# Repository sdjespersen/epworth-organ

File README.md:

# Epworth Organ

Encoders (`primary-encoder` being the primary), decoders (`primary-decoder` being the primary), etc. for the Epworth
organ, targeting the [Raspberry Pi Pico 2](https://datasheets.raspberrypi.com/pico/pico-2-datasheet.pdf), written in
Rust.

## Setup

The best dev setup for this involves using a
[Pico debug probe](https://www.raspberrypi.com/documentation/microcontrollers/debug-probe.html)
and [probe-rs](https://probe.rs). This allows you to get a SWD debugger and UART output, as well as flashing the program
to the chip without holding BOOTSEL while plugging in the USB. (Trust me, it gets old!)

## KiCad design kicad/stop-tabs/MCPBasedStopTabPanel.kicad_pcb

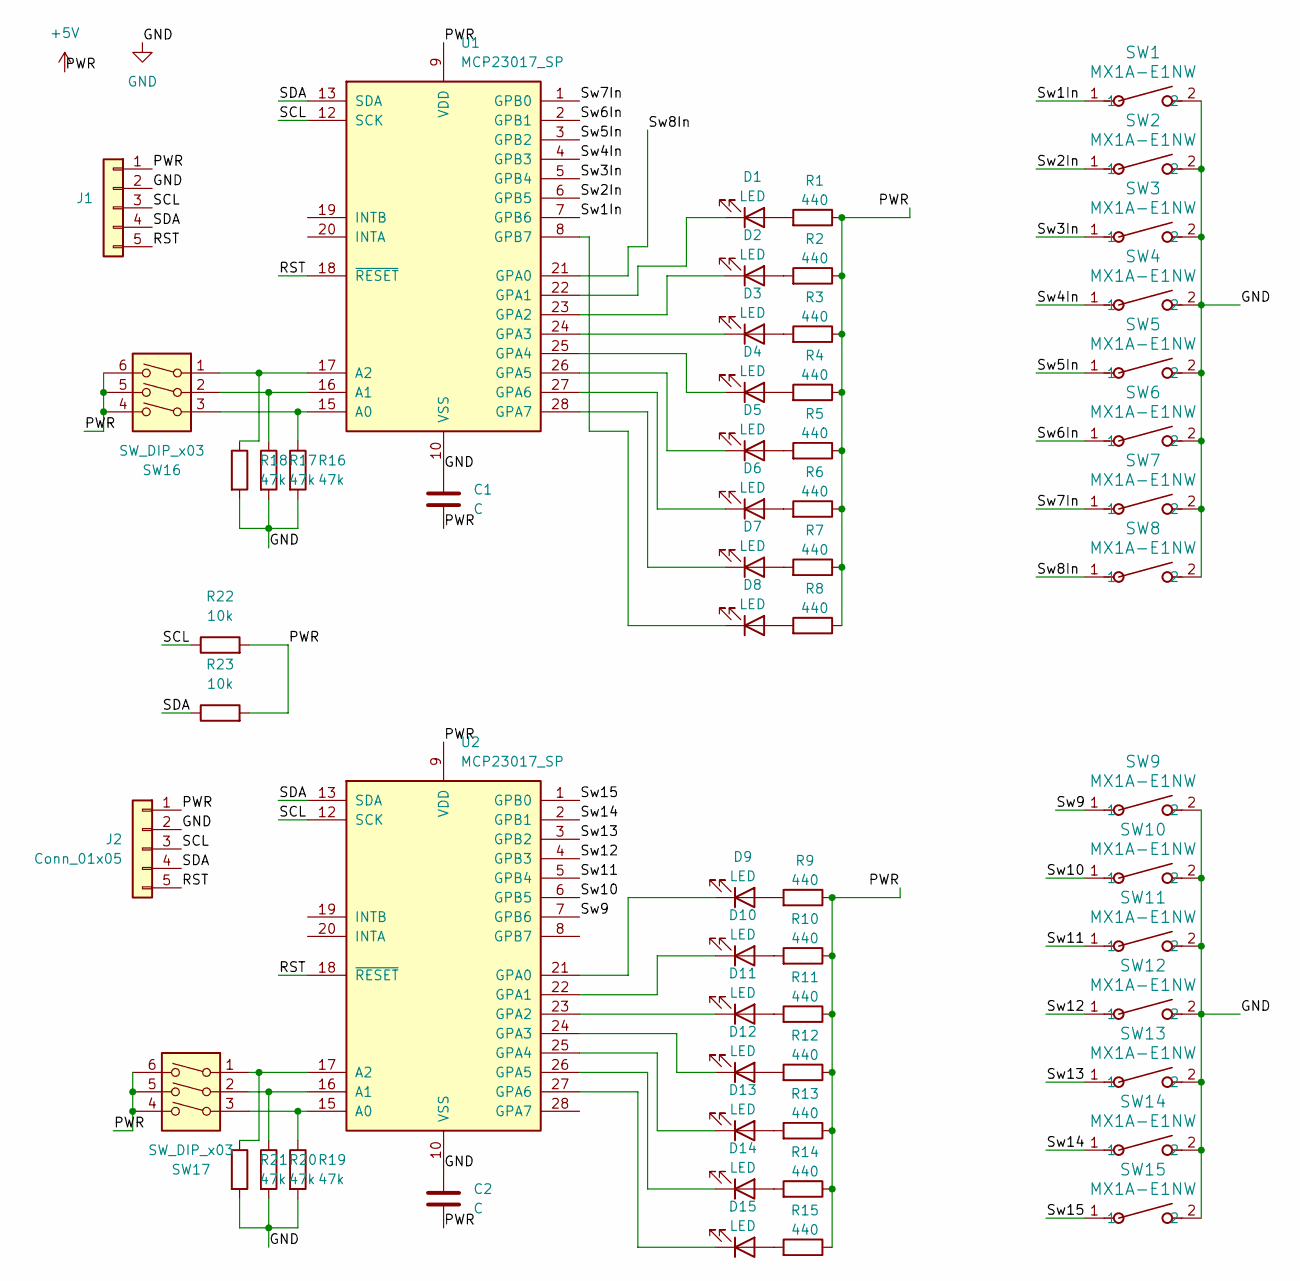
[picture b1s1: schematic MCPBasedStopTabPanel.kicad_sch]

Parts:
C1, C2: C; CAPRR508W50L508T317H508
D1, D2, D3, D4, D5, D6, D7, D8, D9, D10, D11, D12, D13, D14, D15: LED; LED_D5.0mm
J1, J2: Conn_01x05; JST_XH_B5B-XH-A_1x05_P2.50mm_Vertical
R1, R2, R3, R4, R5, R6, R7, R8, R9, R10, R11, R12, R13, R14, R15: 440; R_Axial_DIN0207_L6.3mm_D2.5mm_P7.62mm_Horizontal
R16, R17, R18, R19, R20, R21: 47k; R_Axial_DIN0207_L6.3mm_D2.5mm_P7.62mm_Horizontal
R22, R23: 10k; R_Axial_DIN0207_L6.3mm_D2.5mm_P7.62mm_Horizontal
SW1, SW2, SW3, SW4, SW5, SW6, SW7, SW8, SW9, SW10, SW11, SW12, SW13, SW14, SW15: MX1A-E1NW; SW_Cherry_MX_1.00u_PCB
SW16, SW17: SW_DIP_x03; SW_DIP_SPSTx03_Slide_9.78x9.8mm_W7.62mm_P2.54mm
U1, U2: MCP23017_SP; DIP-28_W7.62mm

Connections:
+5V: C1.2, C2.2, J1.1, J2.1, R1.1, R2.1, R3.1, R4.1, R5.1, R6.1, R7.1, R8.1, R9.1, R10.1, R11.1, R12.1, R13.1, R14.1, R15.1, R22.2, R23.2, SW16.4, SW16.5, SW16.6, SW17.4, SW17.5, SW17.6, U1.9 (VDD), U2.9 (VDD)
/RST: J1.5, J2.5, U1.18 (~RESET), U2.18 (~RESET)
/SCL: J1.3, J2.3, R22.1, U1.12 (SCK), U2.12 (SCK)
/SDA: J1.4, J2.4, R23.1, U1.13 (SDA), U2.13 (SDA)
/Sw1In: SW1.1, U1.7 (GPB6)
/Sw2In: SW2.1, U1.6 (GPB5)
/Sw3In: SW3.1, U1.5 (GPB4)
/Sw4In: SW4.1, U1.4 (GPB3)
/Sw5In: SW5.1, U1.3 (GPB2)
/Sw6In: SW6.1, U1.2 (GPB1)
/Sw7In: SW7.1, U1.1 (GPB0)
/Sw8In: SW8.1, U1.21 (GPA0)
/Sw9: SW9.1, U2.7 (GPB6)
/Sw10: SW10.1, U2.6 (GPB5)
/Sw11: SW11.1, U2.5 (GPB4)
/Sw12: SW12.1, U2.4 (GPB3)
/Sw13: SW13.1, U2.3 (GPB2)
/Sw14: SW14.1, U2.2 (GPB1)
/Sw15: SW15.1, U2.1 (GPB0)
GND: C1.1, C2.1, J1.2, J2.2, R16.2, R17.2, R18.2, R19.2, R20.2, R21.2, SW1.2, SW2.2, SW3.2, SW4.2, SW5.2, SW6.2, SW7.2, SW8.2, SW9.2, SW10.2, SW11.2, SW12.2, SW13.2, SW14.2, SW15.2, U1.10 (VSS), U2.10 (VSS)
unnamed: D1.2 (A), R1.2
unnamed: D1.1 (K), U1.22 (GPA1)
unnamed: D2.2 (A), R2.2
unnamed: D2.1 (K), U1.23 (GPA2)
unnamed: D3.2 (A), R3.2
unnamed: D3.1 (K), U1.24 (GPA3)
unnamed: D4.2 (A), R4.2
unnamed: D4.1 (K), U1.25 (GPA4)
unnamed: D5.2 (A), R5.2
unnamed: D5.1 (K), U1.26 (GPA5)
unnamed: D6.2 (A), R6.2
unnamed: D6.1 (K), U1.27 (GPA6)
unnamed: D7.2 (A), R7.2
unnamed: D7.1 (K), U1.28 (GPA7)
unnamed: D8.2 (A), R8.2
unnamed: D8.1 (K), U1.8 (GPB7)
unnamed: D9.2 (A), R9.2
unnamed: D9.1 (K), U2.21 (GPA0)
unnamed: D10.2 (A), R10.2
unnamed: D10.1 (K), U2.22 (GPA1)
unnamed: D11.2 (A), R11.2
unnamed: D11.1 (K), U2.23 (GPA2)
unnamed: D12.2 (A), R12.2
unnamed: D12.1 (K), U2.24 (GPA3)
unnamed: D13.2 (A), R13.2
unnamed: D13.1 (K), U2.25 (GPA4)
unnamed: D14.2 (A), R14.2
unnamed: D14.1 (K), U2.26 (GPA5)
unnamed: D15.2 (A), R15.2
unnamed: D15.1 (K), U2.27 (GPA6)
unnamed: R16.1, SW16.3, U1.15 (A0)
unnamed: R17.1, SW16.2, U1.16 (A1)
unnamed: R18.1, SW16.1, U1.17 (A2)
unnamed: R19.1, SW17.3, U2.15 (A0)
unnamed: R20.1, SW17.2, U2.16 (A1)
unnamed: R21.1, SW17.1, U2.17 (A2)

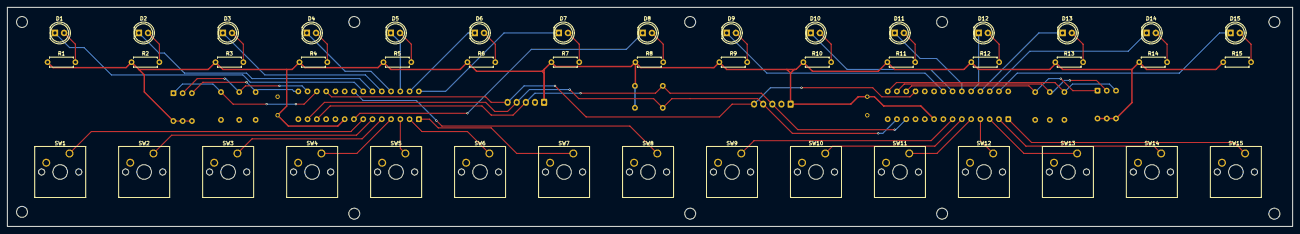
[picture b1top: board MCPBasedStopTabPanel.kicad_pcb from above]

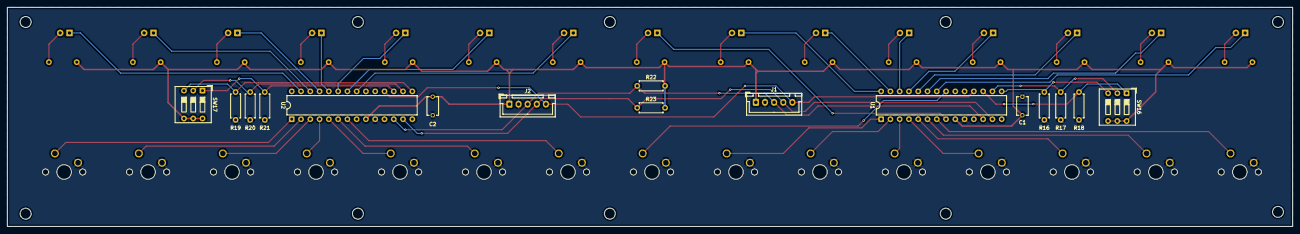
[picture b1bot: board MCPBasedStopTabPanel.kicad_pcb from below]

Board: 2 copper layers, 352.0 x 60.0 mm, 61 parts (16 on the bottom side), 56 nets.

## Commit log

2025-12-10 Add very rough draft of decoder (and readme).
2025-12-15 Fake encoder for testing
2025-12-15 Nearly there on the MIDI decoder.
2025-12-15 Order fixed!
2025-12-16 Update initial flush
2025-12-16 Cleaning up some errant comments
2025-12-16 Small cleanups
2025-12-24 Draft of stop tab buttons
2025-12-24 s/button/key/g
2025-12-24 Avoid some unnecessary writes by using a counter
2025-12-26 Add KiCad project/schematic/PCB design for stop tab panel.
2026-01-01 Button presses are detectable now!
2026-01-01 I think it's working!
2026-01-01 Ignore some KiCad artifacts
2026-01-02 Encoder and decoder working on Teensy!
    Tested it out, and the Teensys talk to each other just fine over a
    single line ("unidirectional UART"?). I tried to get this working
    with an Arduino Nano Every playing the role of encoder, but had
    trouble transmitting MIDI data properly.
2026-01-02 Encoder code works on Arduino Nano Every!
2026-01-02 Pistons functional!
2026-01-03 Major refactoring.
    Got some help from Gemini for this one. (Very useful!) The goal was
    to factor out some of the debouncing logic that checks for stable
    history, detects falling/rising edges, and iterates over those.
2026-01-03 Basic crescendo pedal logic working (correct order, too!)
2026-01-03 One final trick suggested by Gemini
2026-01-06 Oopsie, had an array indexing problem there
2026-01-07 Port to Arduino Nano and fix a bug.
2026-01-07 Fix bug with LED D9.
2026-01-14 Encoder is now in Rust.
2026-01-14 Small refactor in debouncer
2026-01-14 Aaaand decoder ported to Rust, too.
    There was a small bugfix in the encoder.
2026-01-14 Move README contents to top level README
2026-01-14 Goodbye build scripts!
    `cargo run --release` FTW
2026-01-14 Add heartbeat LED and small loop delay.
2026-01-14 Simplify tickers
2026-01-14 README updates
2026-01-28 First draft of RP2350. Going well!
    Uses Embassy, async, all the bells and whistles.
2026-01-28 Make heartbeat the "main" task
2026-01-28 Add lil note about stop state flushing
2026-01-29 Batch LED changes
2026-01-29 Add first bits of USB MIDI functionality.
    CC only for now.
    I think i have an issue during preset recall: In fact, i should emit
    all corresponding MIDI CCs, but right now it does not do that.
2026-01-29 Set a timeout on USB writes.
    This solves the issue wherein we block forever because nobody is
    "listening" on the USB port.
2026-01-29 Make usb config-related static cells `ConstStaticCell`.
2026-01-30 Preset recall now emits MIDI CCs.
    This also rather simplifies a few things:
    - Batching of LED updates is accomplished simply by waiting 1ms
    - Removes "internal MIDI bus"
2026-02-04 Move around some tasks
2026-02-04 Enlarge outbound USB MIDI buffer
2026-02-04 Lengthen timeout, clear entire buffer in this case.
    Even with jitter, the USB really ought to read everything within 2ms.
    If it's not doing so, we need to clear the entire bus, because all
    subsequent messages will also time out. This should clear out the
    message queue more quickly in the scenario where the USB is disconnected.
2026-02-04 First stab at UART MIDI output (not working).
2026-02-05 Pretty sure it IS working!
2026-02-06 New way of handling USB gone.
    I wasn't noticing this failure mode until i moved the USB cable
    over to a different Pico: When a USB cable isn't plugged in at all,
    the `midi_class.wait_connection()` future never completes, so we never
    read off the event queue, eventually blocking all writes. Switching
    from `send` to `try_send` basically just ignores this problem.
2026-02-06 Crazy new idea: Put "decoder" on the encoder.
    The motivator here was twofold:
    1. I'm struggling to send MIDI from Pico to Pico over UART.
    2. Why should they be separate, anyway?
    Eventually i will have to solve the MIDI-over-UART problem. I'm not
    sure why that isn't working right now. But at present, this system
    works really well...
2026-02-06 I'm not using UART0; no need for the interrupt handler.
2026-02-06 Clean up some commented out code
2026-02-06 USB MIDI writes just a bit simpler.
    The pattern is nearly set up for other types of messages.
2026-02-06 It's just a function
2026-02-06 We're committing to combined enc/dec.
    Mostly this change just moves around the hardware layout.
2026-02-06 Remove old comments
2026-02-06 Big rename, now that it's no longer just an encoder
2026-02-07 Factor out preset store in preparation for persistence.
2026-02-07 Preset are persistent!!
2026-02-07 PAGE_SIZE already exists in the lib
2026-02-07 Lil cleanup
2026-02-07 In the middle of adding event queues
2026-02-08 Nice progress here
2026-02-08 Little bit more concise
2026-02-08 Big reorg in preparation for more binaries
2026-02-09 Very very WIP but encoder still OK
2026-02-09 Queues very pure
2026-02-09 Add minimal MIDI stuff
2026-02-09 Getting pretty close on the new paradigm!
2026-02-09 Add GC to midi
2026-02-09 IDK if this works. Quick draft of UART writes.
2026-02-10 Maybe even better
2026-02-10 UART read/write looks pretty good!
2026-02-10 Go back to stops decoding on main MCU.
    I really do think this makes a lot of sense: Almost all the complex
    state computations (crescendo pedal logic, couplings, presets)
    happens in one place, so the rest of the system will just be
    message passing and pure encoding/decoding.
2026-02-11 USB writing looks good
2026-02-11 Add primary decoder draft, still very rough.
2026-02-11 UART writing with serde/postcard looks good
2026-02-11 Buffered UART for the win
2026-02-11 Slight rename
2026-02-11 Partial success...things really sucking over UART
    I'm trying postcard COBS. I think i'm suffering from buffering
    issues, though on the reader or writer i can't be sure.
2026-02-11 Broken comms this way too... :(
2026-02-11 I think this was the problem...
    The async `write` method was allowed to return without writing the
    whole buffer! Goodness gracious. `write_all` ensures we finish.
2026-02-11 Goodness gracious
2026-02-11 Fix reversi situation
2026-02-11 Add launch configs for debugger probe
2026-02-11 change uart pins on decoder
2026-02-11 Crescendo readings on encoder are pretty good
2026-02-11 Add crescendo logic on decoder.
    I already had this pretty much implemented, so mostly copy-paste.
    There is still a little room for improvement in noise reduction
    on the encoder.
2026-02-11 Remove lil comment
2026-02-11 Move output enable step.
2026-02-12 Extract and fix some USB logic.
    This needed changing when i flipped the internal representation of
    the stop state (LSB-first, bit 16 unused). Seems good now.
2026-02-12 Feature/rp2350 (#1)
    * First draft of RP2350. Going well!
    Uses Embassy, async, all the bells and whistles.
    * Make heartbeat the "main" task
    * Add lil note about stop state flushing
    * Batch LED changes
    * Add first bits of USB MIDI functionality.
2026-02-12 Use same reading logic for UART
2026-02-12 USB reading works!
2026-02-12 Off-by-one error on the "general" channel for crescendo
2026-02-16 Break out encoder and decoder state (pure logic)
2026-02-16 Invert dependency on preset store impl
2026-02-17 Major updates to decoder.
    Stops have all been named.
2026-02-17 Internal representation of Stop is only one u8 now
2026-02-17 Update comments
2026-02-17 Pull out a bit more USB MIDI stuff.
2026-02-17 Remove unnecessary derived traits
2026-02-17 Cleanups
2026-02-17 More cleanups
2026-02-17 Remove a single TODO (not gonna happen)
2026-02-17 Factor out common UART reading logic
2026-02-17 Document MIDI contract, reorg
2026-02-17 Address rustc warnings
2026-02-18 Scan pistons with SPI!
2026-02-18 Remove crescendo from primary encoder.
    It will live on a separate Pico. It was there just for testing.
2026-02-18 Change board layout.
2026-02-20 Move stop state writing to SPI bus
2026-02-21 Move UART0 to presumably final location.
2026-02-22 Fix a bug in saving presets and use first 16 switches.
    TODO: Remaining 16 switches.
2026-02-22 Debouncer now u64-based. Pistons should work.
2026-03-08 Progress checkin.
    Swell + pedal boards are currently fried. Waiting for replacement MCP23017s.
    Putting all logic on a single board for now, since we are abandoning all hope of MIDI for the moment.
    On the plus side, using 2.2k pull-ups on the i2c bus is working well, and getting rid of the pull-downs for address pins and hard-wiring them to +5V and GND is also a good move.
2026-03-08 Fix shift out pins
